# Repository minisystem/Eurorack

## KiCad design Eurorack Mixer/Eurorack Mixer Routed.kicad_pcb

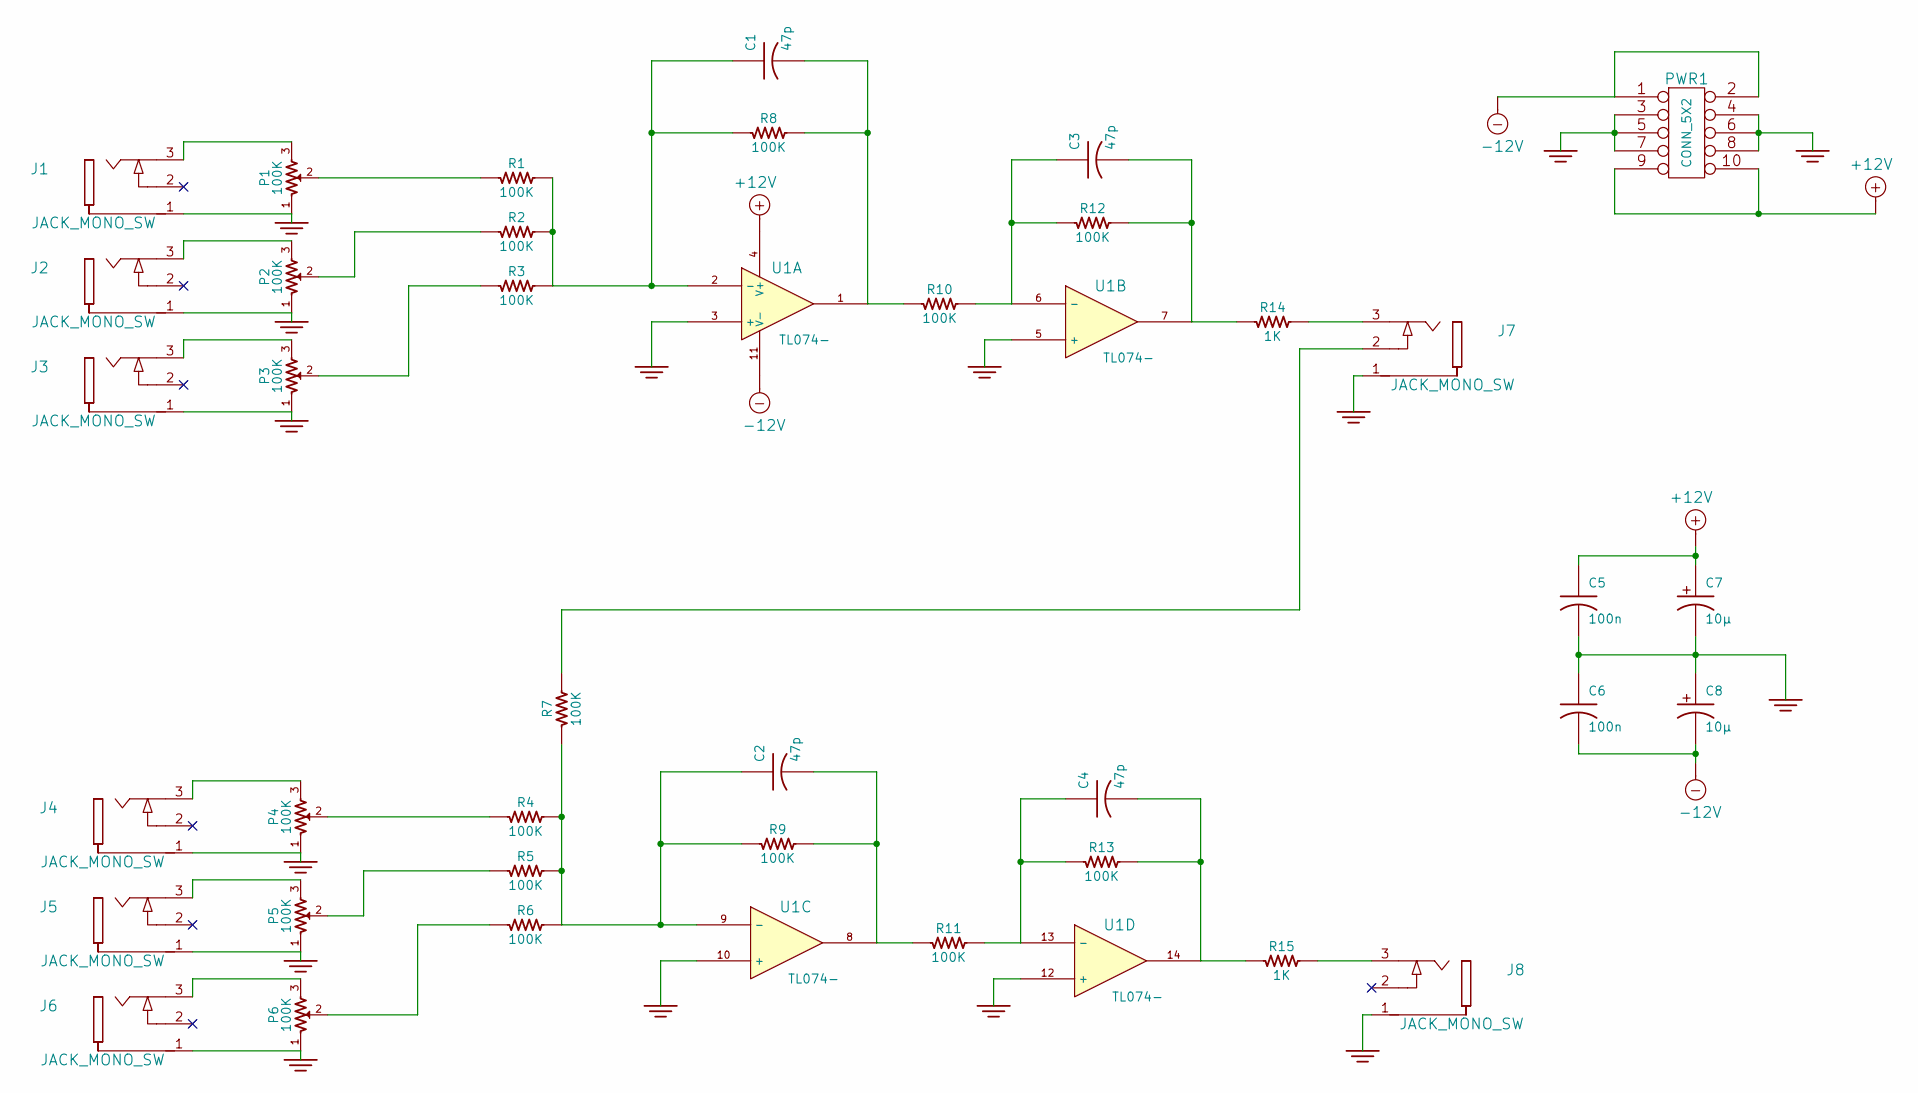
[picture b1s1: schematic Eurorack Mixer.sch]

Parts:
C1, C2, C3, C4: 47p
C5, C6: 100n
C7, C8: 10μ
J1, J2, J3, J4, J5, J6, J7, J8: JACK_MONO_SW
P1, P2, P3, P4, P5, P6: 100K
PWR1: CONN_5X2
R1, R2, R3, R4, R5, R6, R7, R8, R9, R10, R11, R12, R13: 100K
R14, R15: 1K
U1: TL074-

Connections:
+12V: C5.1, C7.1 (+), PWR1.9, PWR1.10, U1.4 (V+)
-12V: C6.2, C8.2 (-), PWR1.1, PWR1.2, U1.11 (V-)
GND: C5.2, C6.1, C7.2 (-), C8.1 (+), J1.1, J2.1, J3.1, J4.1, J5.1, J6.1, J7.1, J8.1, P1.1, P2.1, P3.1, P4.1, P5.1, P6.1, PWR1.3, PWR1.4, PWR1.5, PWR1.6, PWR1.7, PWR1.8, U1.3 (+), U1.5 (+), U1.10 (+), U1.12 (+)
unnamed: C4.2, R13.2, R15.1, U1.14
unnamed: C4.1, R11.2, R13.1, U1.13 (-)
unnamed: J6.3, P6.3
unnamed: C2.2, R9.2, R11.1, U1.8
unnamed: J8.3, R15.2
unnamed: P6.2, R6.1
unnamed: P4.2, R4.1
unnamed: J4.3, P4.3
unnamed: J5.3, P5.3
unnamed: P5.2, R5.1
unnamed: J7.2, R7.2
unnamed: P2.2, R2.1
unnamed: P3.2, R3.1
unnamed: P1.2, R1.1
unnamed: C1.1, R1.2, R2.2, R3.2, R8.1, U1.2 (-)
unnamed: C1.2, R8.2, R10.1, U1.1
unnamed: J2.3, P2.3
unnamed: J3.3, P3.3
unnamed: J1.3, P1.3
unnamed: C2.1, R4.2, R5.2, R6.2, R7.1, R9.1, U1.9 (-)
unnamed: J7.3, R14.2
unnamed: C3.2, R12.2, R14.1, U1.7
unnamed: C3.1, R10.2, R12.1, U1.6 (-)

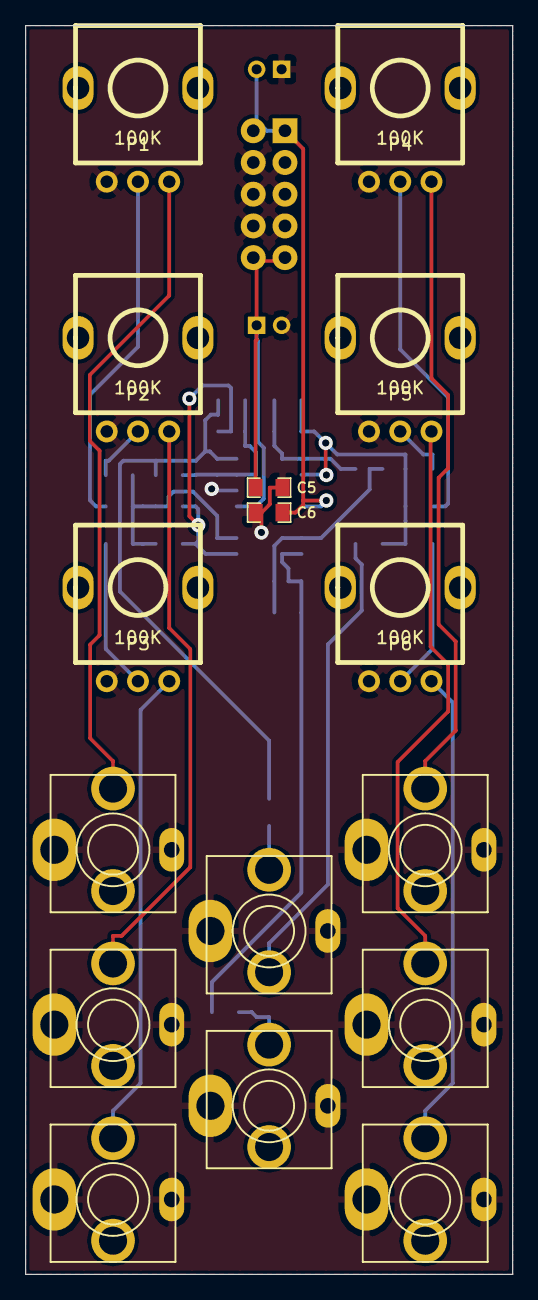
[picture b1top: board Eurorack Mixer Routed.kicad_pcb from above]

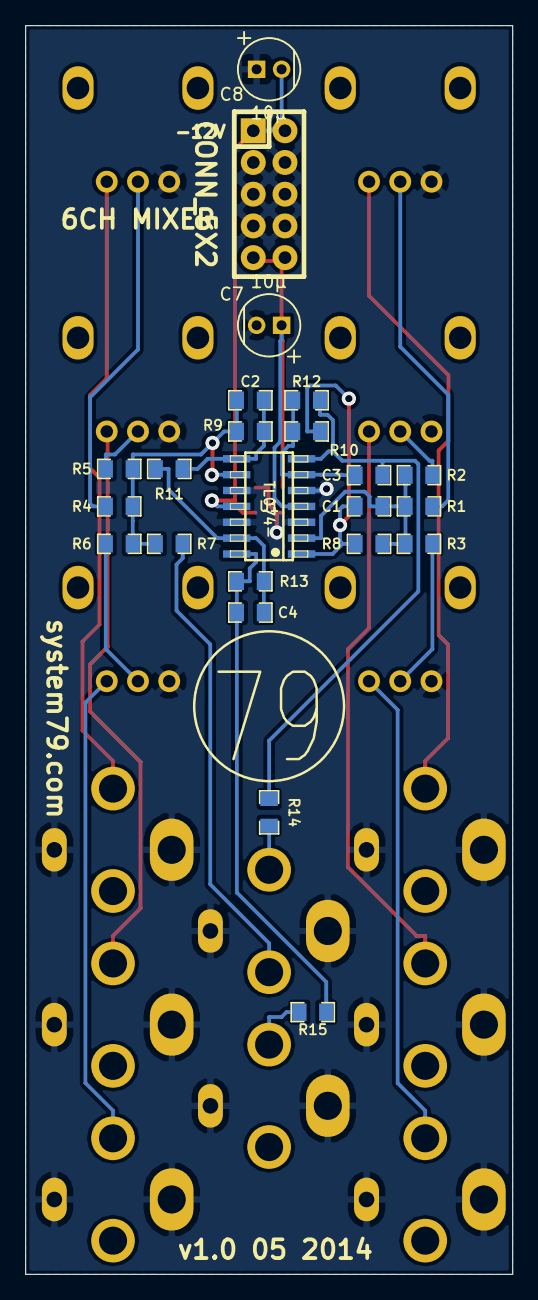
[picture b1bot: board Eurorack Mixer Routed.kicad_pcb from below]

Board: 2 copper layers, 39.0 x 100.0 mm, 40 parts (24 on the bottom side), 26 nets.

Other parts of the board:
system79-logo-12mm: VAL**; system79-logo-12mm

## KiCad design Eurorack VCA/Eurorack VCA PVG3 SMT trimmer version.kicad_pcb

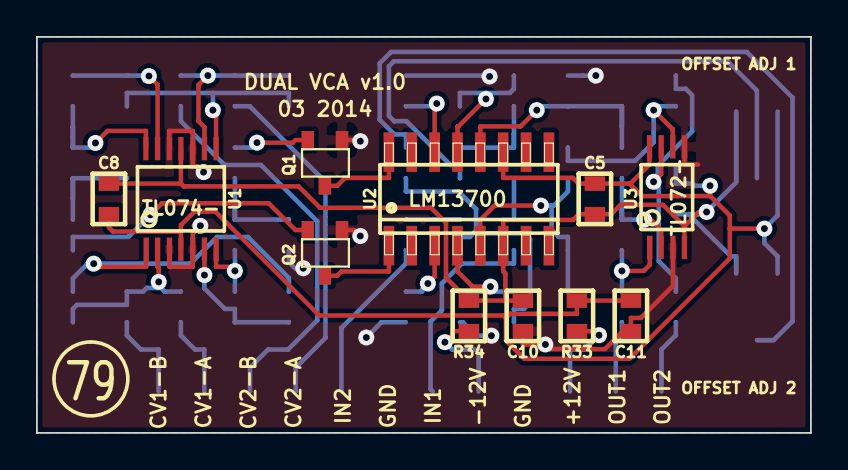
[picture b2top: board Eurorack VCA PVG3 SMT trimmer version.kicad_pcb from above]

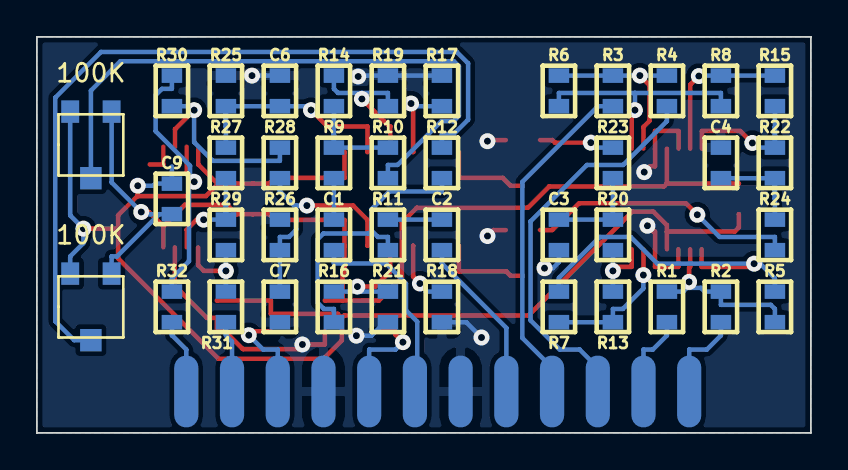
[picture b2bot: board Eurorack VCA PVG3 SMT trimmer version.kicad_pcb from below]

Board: 2 copper layers, 43.0 x 22.0 mm, 53 parts (42 on the bottom side), 43 nets.

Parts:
C1, C2, C10, C11: 1μ; SM0603-JRL
C3, C4: 0.1μ; SM0603-JRL
C5, C8, C9: 100n; SM0603-JRL
C6, C7: 47p; SM0603-JRL
P1, P2: 100K; PVG3
P3: CONN_12; CONN_12X_0100_SMD
Q1, Q2: 2N3906; SOT23-JRL
R1, R2, R3, R4, R5, R6, R7, R8, R13, R15, R27, R28, R29, R30: 100K; SM0603-JRL
R9, R11: 82K; SM0603-JRL
R10, R12: 2.2M; SM0603-JRL
R14, R16: 4.7K; SM0603-JRL
R17, R18, R19, R21: 560; SM0603-JRL
R20, R22: 10K; SM0603-JRL
R23, R24: 22K; SM0603-JRL
R25, R26: 47K; SM0603-JRL
R31, R32: 1K; SM0603-JRL
R33, R34: 10; SM0603-JRL
U1: TL074-; TSSOP14
U2: LM13700; SO16-JRL
U3: TL072-; TSSOP8-JRL

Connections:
+12V: C5.1, C8.1, C9.1, C11.1, P1.1, P2.1, R33.1, U1.4, U2.11, U3.8
-12V: C5.2, C8.2, C9.2, C10.2, P1.3, P2.3, R34.1, U1.11, U2.6, U3.4
CV1A: P3.11, R1.1
CV1B: P3.12, R2.1
CV2A: P3.9, R3.1
CV2B: P3.10, R4.1
GND: C3.2, C4.2, C6.2, C7.2, C10.1, C11.2, P3.4, P3.7, Q1.2, Q2.2, R17.2, R18.2, R19.2, R21.2, R25.2, R26.2, U1.3, U1.5, U1.10, U1.12, U3.3, U3.5
IN1: C1.1, P3.6
IN2: C2.1, P3.8
unnamed: R30.2, R32.1, U3.7
unnamed: R8.2, R15.1, U1.13
unnamed: R15.2, R22.1, U1.14
unnamed: Q2.3, U2.1
unnamed: R28.2, R30.1, U3.6
unnamed: R17.1, U2.14
unnamed: R14.2, R19.1, U2.13
unnamed: C4.1, R22.2, R24.1
unnamed: Q2.1, R24.2
unnamed: R3.2, R4.2, R6.1, U1.9
unnamed: R6.2, R8.1, U1.8
unnamed: P3.5, R34.2
unnamed: P3.3, R33.2
unnamed: C7.1, R26.1, R28.1, U2.5
unnamed: C2.2, R11.1
unnamed: P2.2, R12.1
unnamed: R11.2, R12.2, R16.1
unnamed: R16.2, R21.1, U2.4
unnamed: R18.1, U2.3
unnamed: C3.1, R20.2, R23.1
unnamed: Q1.1, R23.2
unnamed: R1.2, R2.2, R5.1, U1.2
unnamed: R5.2, R7.1, U1.1
unnamed: C1.2, R9.1
unnamed: C6.1, R25.1, R27.1, U2.12
unnamed: P1.2, R10.1
unnamed: R9.2, R10.2, R14.1
unnamed: R7.2, R13.1, U1.6
unnamed: R13.2, R20.1, U1.7
unnamed: Q1.3, U2.16
unnamed: R29.2, R31.1, U3.1
unnamed: R27.2, R29.1, U3.2
OUT1: P3.2, R31.2
OUT2: P3.1, R32.2
